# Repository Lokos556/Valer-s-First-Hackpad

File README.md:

# Valer's First Hackpad
As you can probably tell it's my first hackpad. It was designed with the intention of including everything that can be useful in a compact size. It has 7 keys, a rotary encoder and a 0.91 inch OLED screen. It uses KMK firmware. Please consider that I'm not advanced in this field.
## Features
* 3D Printed Case
* 3D Printed Insert
* 128x32 0.91 OLED screen
* Rotary Encoder
* 7 Keys
## CAD Model
For ease of printing it uses the standard base(tutorial) however redesigned to fit my parts. It was made wider, taller and the hole in the side for the microprocessor was relocated. The cutouts were adjusted accordingly to everything.(The outside is only reflective because that's the only way I could render it)

Made in Fusion 360
## PCB
My PCB was made in Kicad.
#### Schematic

#### PCB

## Firmware

This HackPad uses KMK firmware.
I haven't assigned specifics to the buttons as I will be doing that after the assembly.
This is the only part which I'm completely unsure if it was done right, if no I would greatly aprreciate help.

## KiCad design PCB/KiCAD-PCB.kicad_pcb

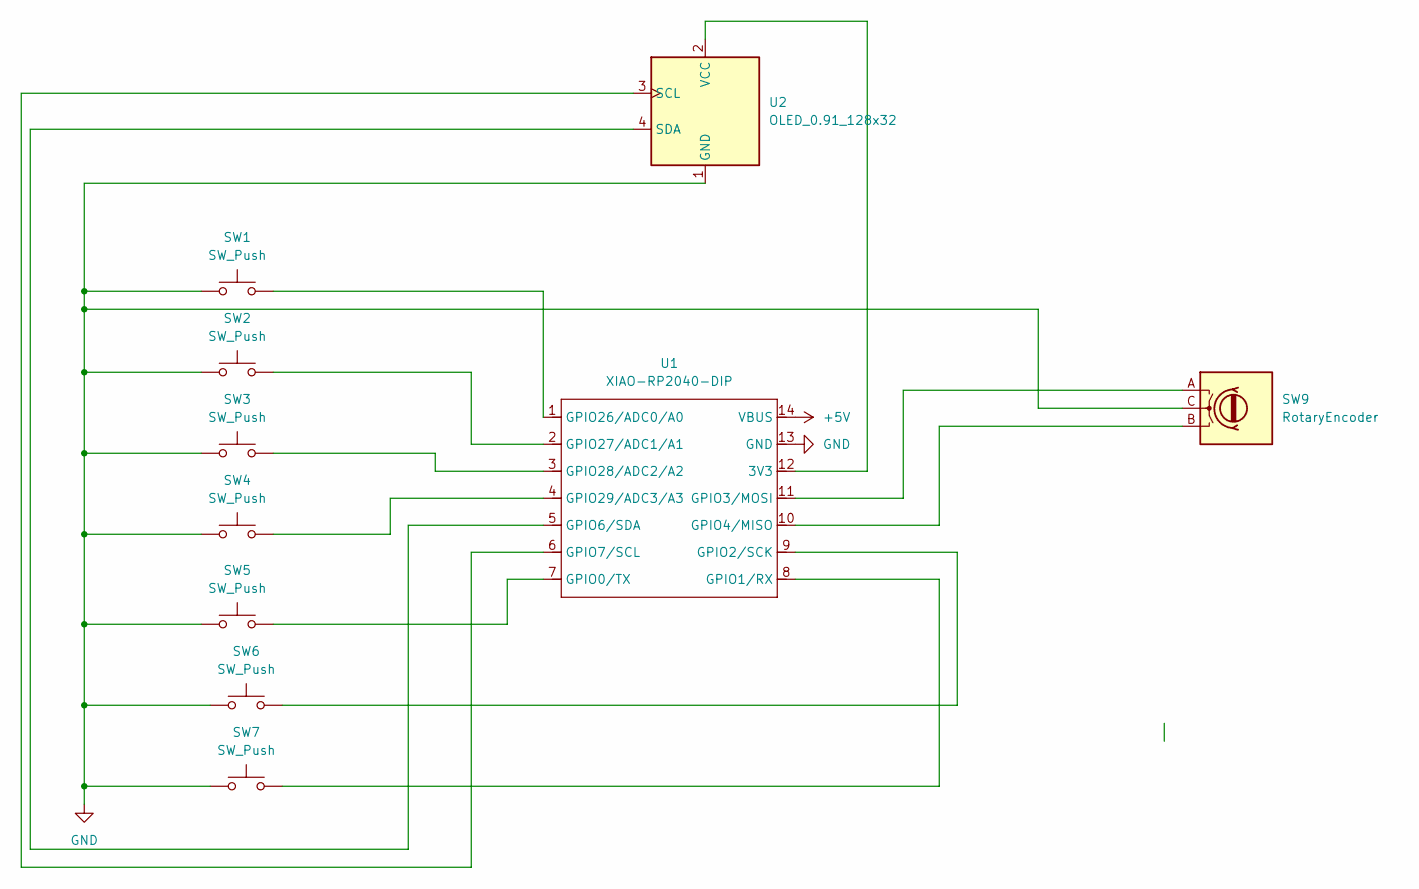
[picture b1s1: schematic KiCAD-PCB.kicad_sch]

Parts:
SW1, SW2, SW3, SW4, SW5, SW6, SW7: SW_Push; SW_Cherry_MX_1.00u_PCB
SW9: RotaryEncoder; RotaryEncoder_Alps_EC11E_Vertical_H20mm
U1: XIAO-RP2040-DIP
U2: OLED_0.91_128x32

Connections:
+5V: U1.14 (VBUS)
GND: SW1.1, SW2.1, SW3.1, SW4.1, SW5.1, SW6.1, SW7.1, SW9.C, U1.13 (GND), U2.1 (GND)
unnamed: U1.12 (3V3), U2.2 (VCC)
unnamed: SW5.2, U1.7 (GPIO0/TX)
unnamed: SW7.2, U1.8 (GPIO1/RX)
unnamed: SW6.2, U1.9 (GPIO2/SCK)
unnamed: SW9.A, U1.11 (GPIO3/MOSI)
unnamed: SW9.B, U1.10 (GPIO4/MISO)
unnamed: U1.5 (GPIO6/SDA), U2.4 (SDA)
unnamed: U1.6 (GPIO7/SCL), U2.3 (SCL)
unnamed: SW1.2, U1.1 (GPIO26/ADC0/A0)
unnamed: SW2.2, U1.2 (GPIO27/ADC1/A1)
unnamed: SW3.2, U1.3 (GPIO28/ADC2/A2)
unnamed: SW4.2, U1.4 (GPIO29/ADC3/A3)

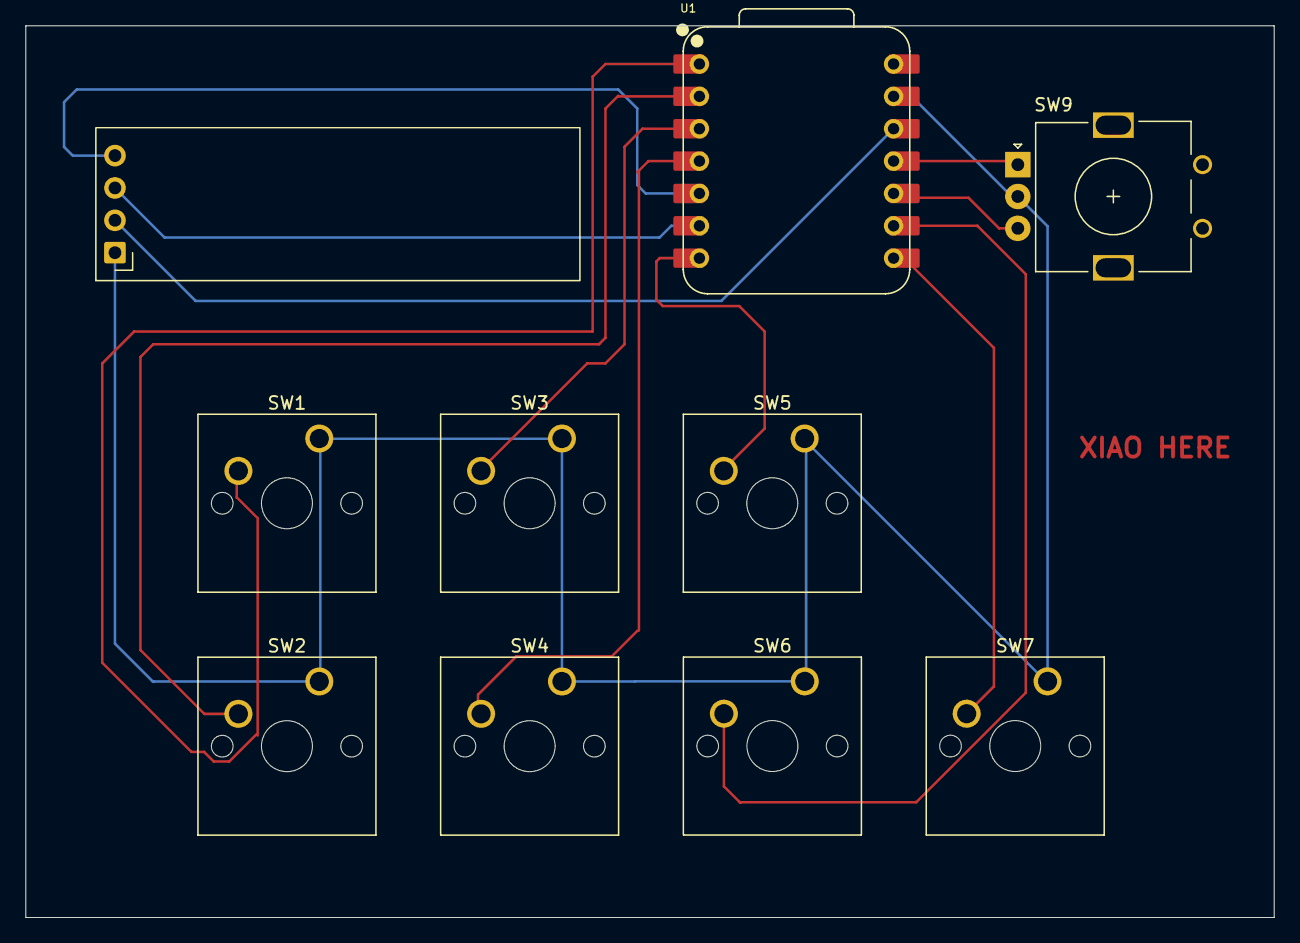
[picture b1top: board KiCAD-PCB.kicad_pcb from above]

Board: 2 copper layers, 98.0 x 70.0 mm, 10 parts (0 on the bottom side), 13 nets.

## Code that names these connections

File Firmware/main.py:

import board

from kmk.kmk_keyboard import KMKKeyboard
from kmk.scanners.keypad import KeysScanner
from kmk.keys import KC
from kmk.modules.encoder import EncoderHandler
from kmk.extensions.display import Display, SSD1306

# ─────────────────────────────
# Keyboard instance
# ─────────────────────────────
keyboard = KMKKeyboard()

# ─────────────────────────────
# Switches (7 direct GPIO pins)
# Matches your schematic exactly
# ─────────────────────────────
PINS = (
    board.A0,   # GPIO26 - SW1
    board.A1,   # GPIO27 - SW2
    board.A2,   # GPIO28 - SW3
    board.A3,   # GPIO29 - SW4
    board.TX,   # GPIO0  - SW5
    board.RX,   # GPIO1  - SW6
    board.SCK,  # GPIO2  - SW7
)

keyboard.matrix = KeysScanner(
    pins=PINS,
    value_when_pressed=False,  # switch shorts to GND
)

# ─────────────────────────────
# Rotary Encoder (A/B only)
# GPIO3 and GPIO4 per schematic
# ─────────────────────────────
encoder = EncoderHandler()
keyboard.modules.append(encoder)

encoder.pins = (
    (board.MOSI, board.MISO),  # GPIO3, GPIO4
)

# Clockwise / Counter-clockwise
encoder.map = [
    ((KC.VOLD, KC.VOLU),)
]

# ─────────────────────────────
# OLED Display (SSD1306 128x32)
# I²C on GPIO6 / GPIO7
# ─────────────────────────────
oled = Display(
    display=SSD1306(
        i2c_bus=1,
        sda=board.D4,  # GPIO6
        scl=board.D5,  # GPIO7
        width=128,
        height=32,
    ),
)

keyboard.extensions.append(oled)

# ─────────────────────────────
# Keymap (7 keys = 7 switches)
# ─────────────────────────────
keyboard.keymap = [
    [
        KC.A,
        KC.B,
        KC.C,
        KC.D,
        KC.E,
        KC.F,
        KC.G,
    ]
]

# ─────────────────────────────
# Start KMK
# ─────────────────────────────
keyboard.go()

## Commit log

2026-01-09 Create s
